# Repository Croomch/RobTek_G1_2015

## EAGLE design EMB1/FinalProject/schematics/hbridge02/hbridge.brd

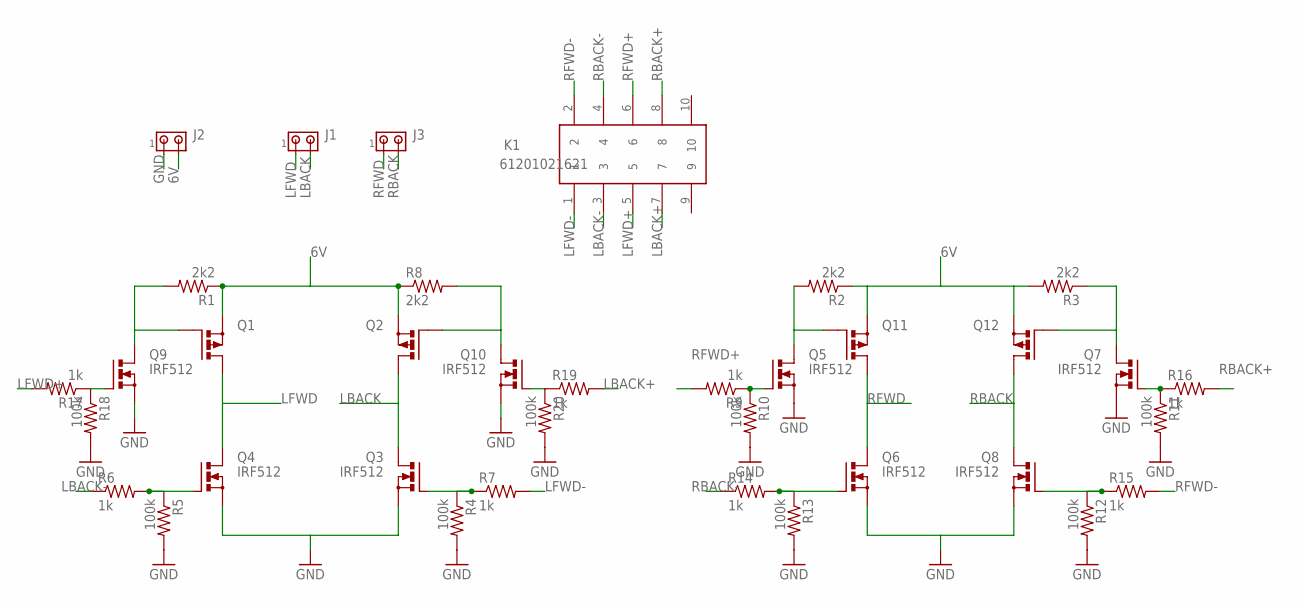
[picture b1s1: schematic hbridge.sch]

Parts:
J1, J2, J3: MTA02-100; 10X02MTA
K1: 61201021621
Q1, Q2, Q11, Q12: PMOSFET_PTO220BV; TO220BV
Q3, Q4, Q5, Q6, Q7, Q8, Q9, Q10: IRF512; TO220BV
R1, R2, R3, R8: 2k2; 0204/7
R4, R5, R10, R11, R12, R13, R18, R20: 100k; 0204/7
R6, R7, R9, R14, R15, R16, R17, R19: 1k; 0204/7

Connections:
6V: J2.2, Q1.S, Q2.S, Q11.S, Q12.S, R1.1, R2.1, R3.2, R8.1
GND: J2.1, Q3.S, Q4.S, Q5.S, Q6.S, Q7.S, Q8.S, Q9.S, Q10.S, R4.2, R5.2, R10.2, R11.2, R12.2, R13.2, R18.2, R20.2
LBACK: J1.2, Q2.D, Q3.D
LBACK+: K1.7, R19.2
LBACK-: K1.3, R6.1
LFWD: J1.1, Q1.D, Q4.D
LFWD+: K1.5, R17.2
LFWD-: K1.1, R7.2
unnamed: Q3.G, R4.1, R7.1
unnamed: Q2.G, Q10.D, R8.2
unnamed: Q4.G, R5.1, R6.2
unnamed: Q1.G, Q9.D, R1.2
unnamed: Q8.G, R12.1, R15.1
unnamed: Q7.G, R11.1, R16.1
unnamed: Q6.G, R13.1, R14.2
unnamed: Q5.G, R9.1, R10.1
unnamed: Q5.D, Q11.G, R2.2
unnamed: Q10.G, R19.1, R20.1
unnamed: Q9.G, R17.1, R18.1
unnamed: Q7.D, Q12.G, R3.1
RBACK: J3.2, Q8.D, Q12.D
RBACK+: K1.8, R16.2
RBACK-: K1.4, R14.1
RFWD: J3.1, Q6.D, Q11.D
RFWD+: K1.6, R9.2
RFWD-: K1.2, R15.2

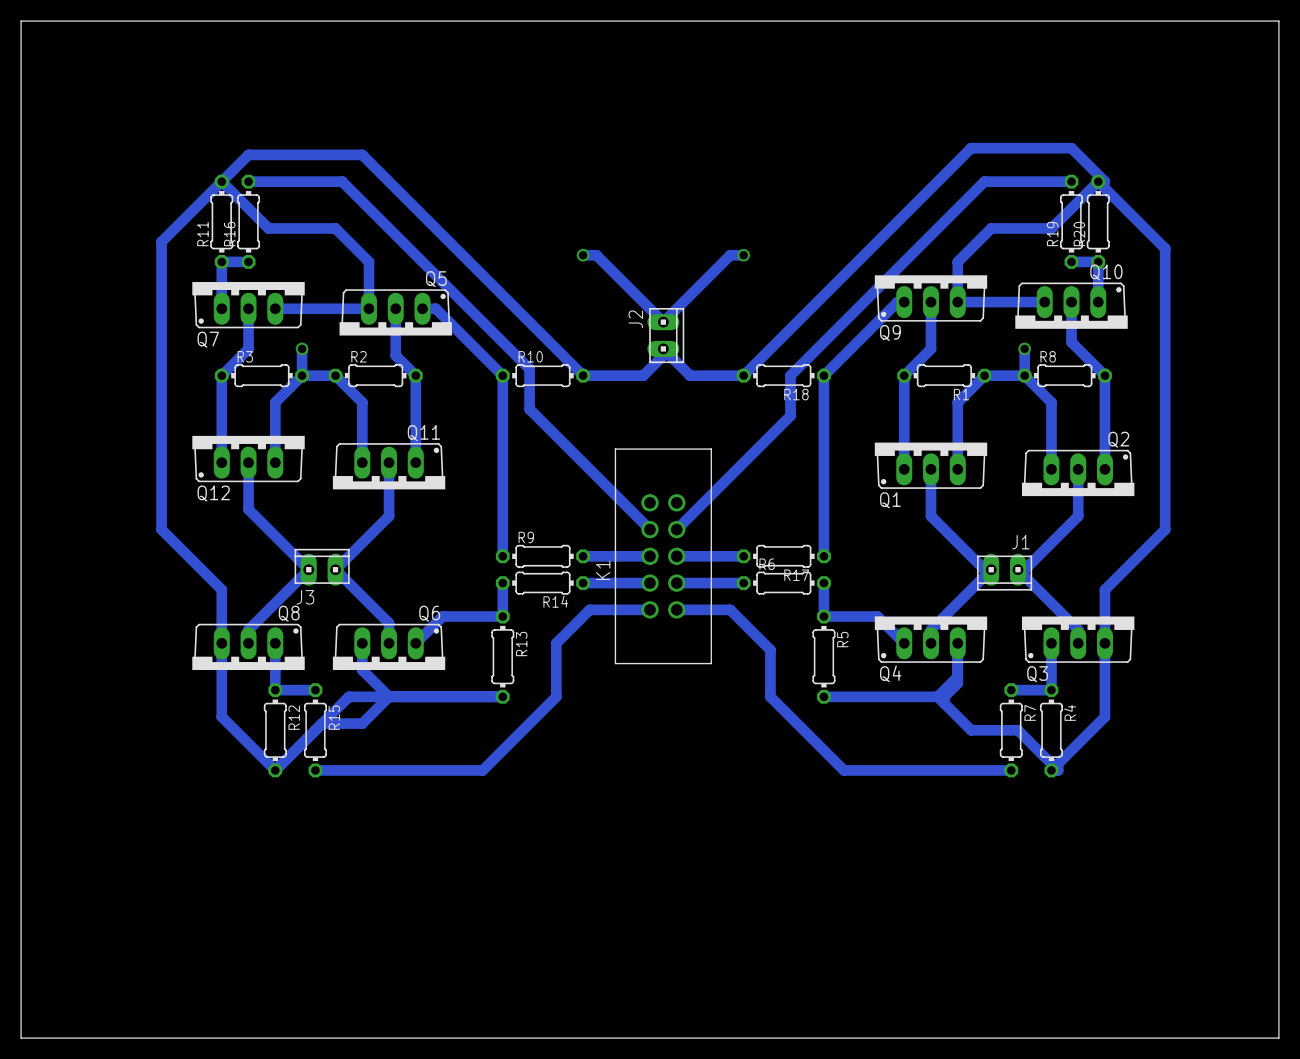
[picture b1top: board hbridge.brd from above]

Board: 2 copper layers, 119.4 x 96.5 mm, 36 parts (0 on the bottom side), 26 nets.

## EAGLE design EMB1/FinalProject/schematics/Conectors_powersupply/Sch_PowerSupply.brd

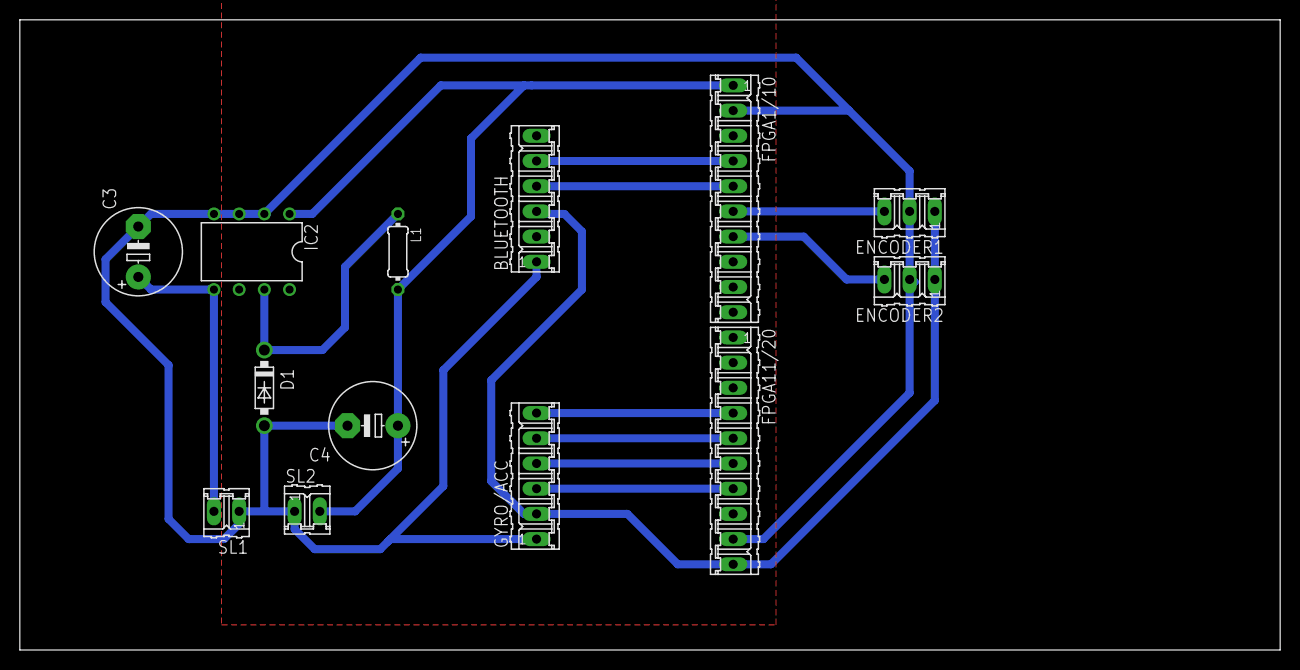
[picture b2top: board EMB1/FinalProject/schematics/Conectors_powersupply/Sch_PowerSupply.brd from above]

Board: 2 copper layers, 127.0 x 63.5 mm, 13 parts (0 on the bottom side), 13 nets.

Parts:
BLUETOOTH: 06P
C3: 22; E5-8,5
C4: 220; E5-8,5
D1: 1N5817-B; DO41-7.6
ENCODER1, ENCODER2: 03P
FPGA1/10, FPGA11/20: 10P
GYRO/ACC: 06P
IC2: LM2574N-3.3; DIL08
L1: 0204/7
SL1, SL2: 02P

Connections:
3.3V: BLUETOOTH.3, ENCODER1.1, ENCODER2.1, FPGA11/20.10, GYRO/ACC.2
5V: C4.+, FPGA1/10.1, IC2.1, L1.2, SL2.2
15V: C3.+, IC2.5, SL1.2
CL: FPGA11/20.4, GYRO/ACC.6
GND: BLUETOOTH.1, C3.-, C4.-, D1.A, ENCODER1.2, ENCODER2.2, FPGA1/10.2, FPGA11/20.9, GYRO/ACC.1, IC2.2, IC2.3, IC2.4, SL1.1, SL2.1
MISO: FPGA11/20.5, GYRO/ACC.5
MOSI: FPGA11/20.7, GYRO/ACC.3
unnamed: D1.C, IC2.7, L1.1
RX-I: BLUETOOTH.5, FPGA1/10.4
SCL: FPGA11/20.6, GYRO/ACC.4
SIGNAL1: ENCODER1.3, FPGA1/10.6
SIGNAL2: ENCODER2.3, FPGA1/10.7
TX-O: BLUETOOTH.4, FPGA1/10.5

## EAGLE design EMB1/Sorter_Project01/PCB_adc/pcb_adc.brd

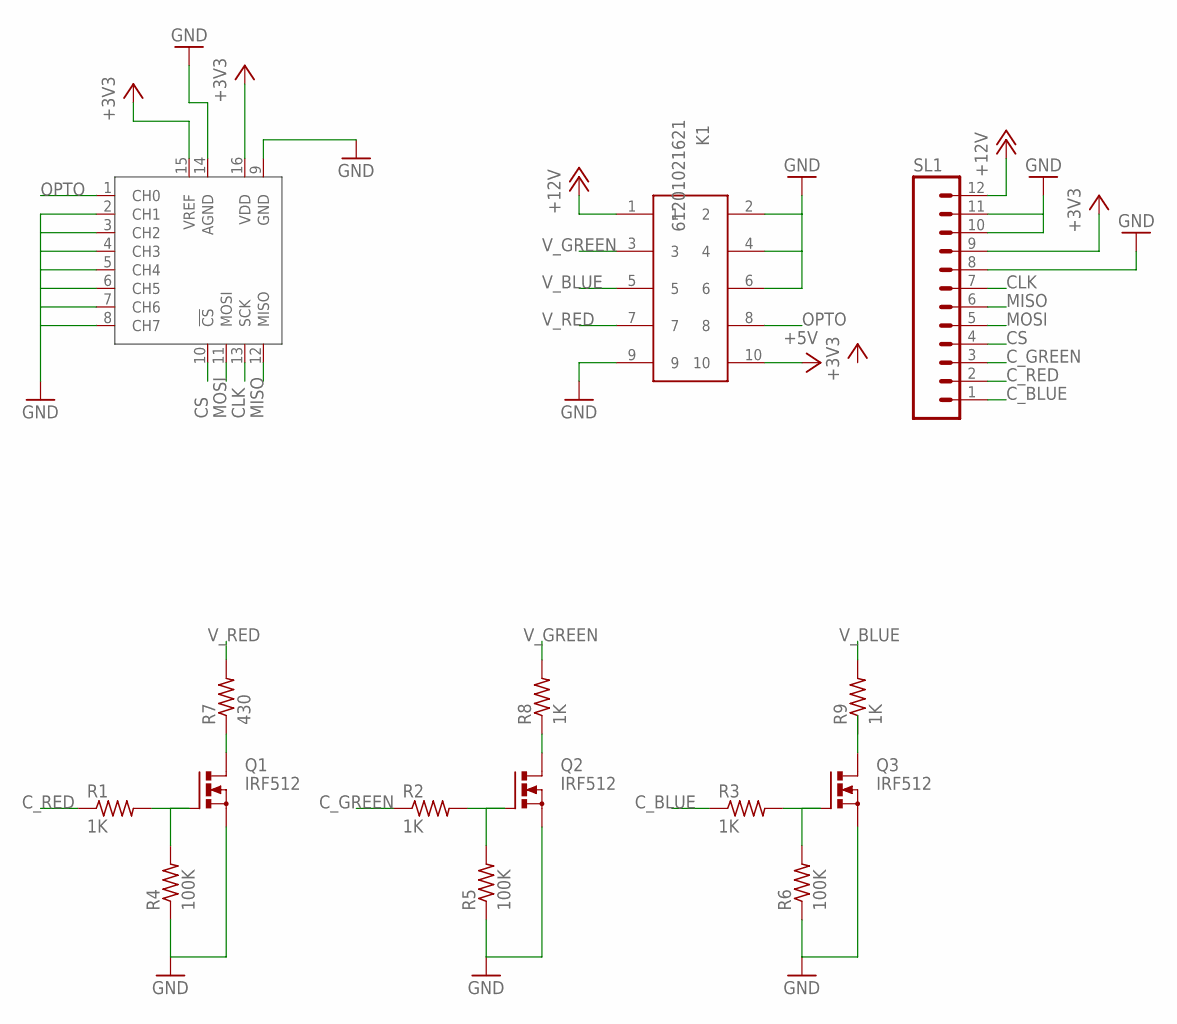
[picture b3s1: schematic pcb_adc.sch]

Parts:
K1: 61201021621
Q1, Q2, Q3: IRF512; TO220BV
R1, R2, R3, R8, R9: 1K; 0204/7
R4, R5, R6: 100K; 0204/7
R7: 430; 0204/7
SL1: M12; 12P
U$1: MCP3008P; DIL16

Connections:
+3V3: SL1.9, U$1.15 (VREF), U$1.16 (VDD)
+5V: K1.10
+12V: K1.1, SL1.12
CLK: SL1.7, U$1.13 (SCK)
CS: SL1.4, U$1.10 (!CS)
C_BLUE: R3.1, SL1.1
C_GREEN: R2.1, SL1.3
C_RED: R1.1, SL1.2
GND: K1.2, K1.4, K1.6, K1.9, Q1.S, Q2.S, Q3.S, R4.1, R5.1, R6.1, SL1.8, SL1.10, SL1.11, U$1.2 (CH1), U$1.3 (CH2), U$1.4 (CH3), U$1.5 (CH4), U$1.6 (CH5), U$1.7 (CH6), U$1.8 (CH7), U$1.9 (GND), U$1.14 (AGND)
MISO: SL1.6, U$1.12 (MISO)
MOSI: SL1.5, U$1.11 (MOSI)
unnamed: Q1.G, R1.2, R4.2
unnamed: Q2.G, R2.2, R5.2
unnamed: Q3.G, R3.2, R6.2
unnamed: Q1.D, R7.1
unnamed: Q2.D, R8.1
unnamed: Q3.D, R9.1
OPTO: K1.8, U$1.1 (CH0)
V_BLUE: K1.5, R9.2
V_GREEN: K1.3, R8.2
V_RED: K1.7, R7.2

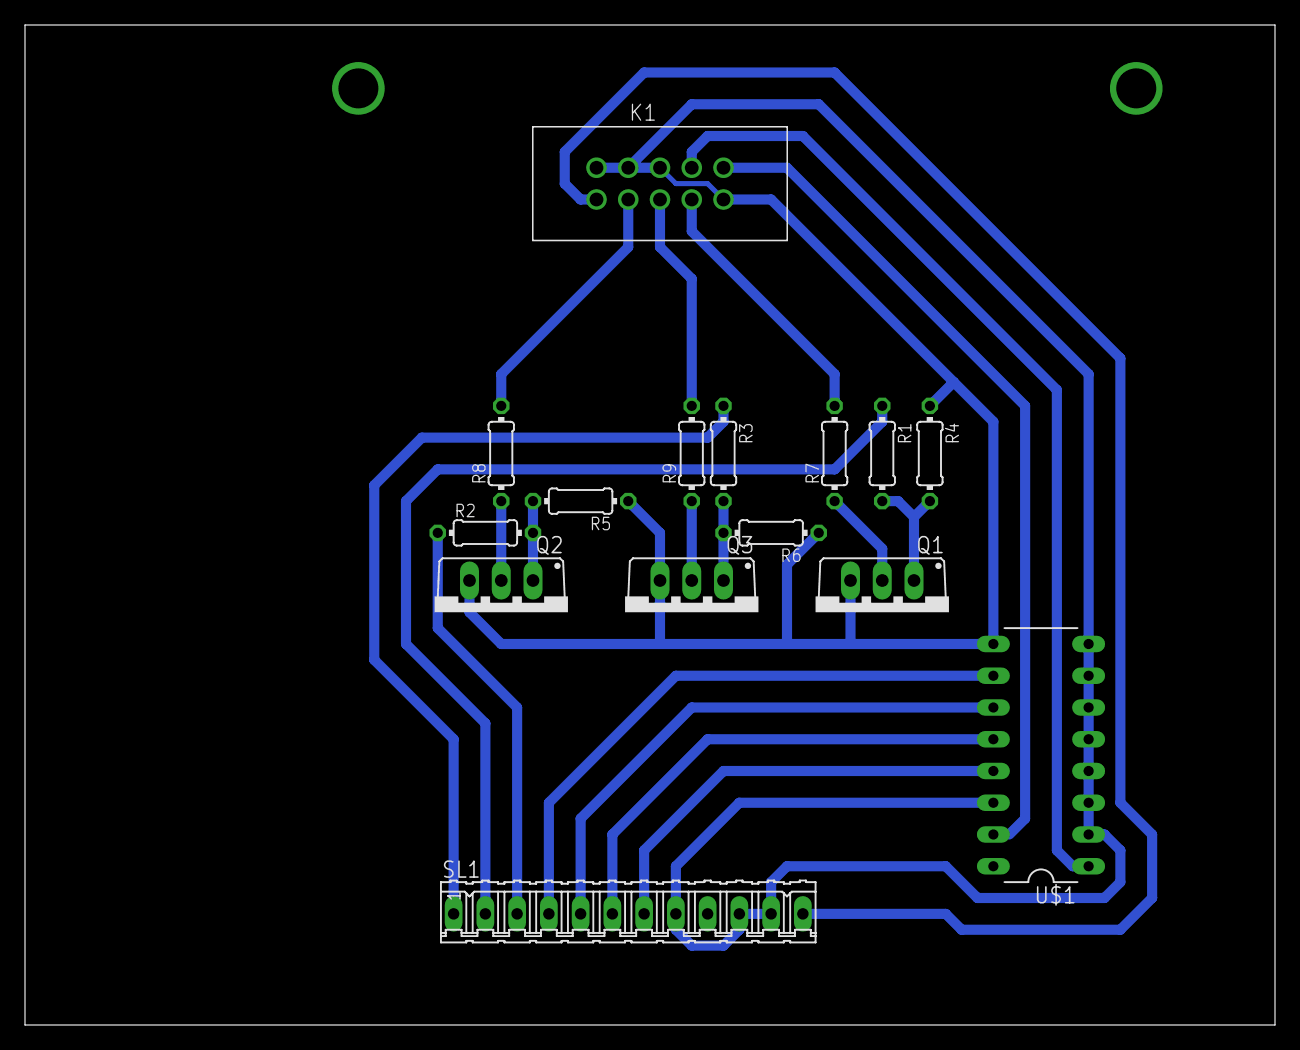
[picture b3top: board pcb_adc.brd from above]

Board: 2 copper layers, 100.0 x 80.0 mm, 15 parts (0 on the bottom side), 20 nets.

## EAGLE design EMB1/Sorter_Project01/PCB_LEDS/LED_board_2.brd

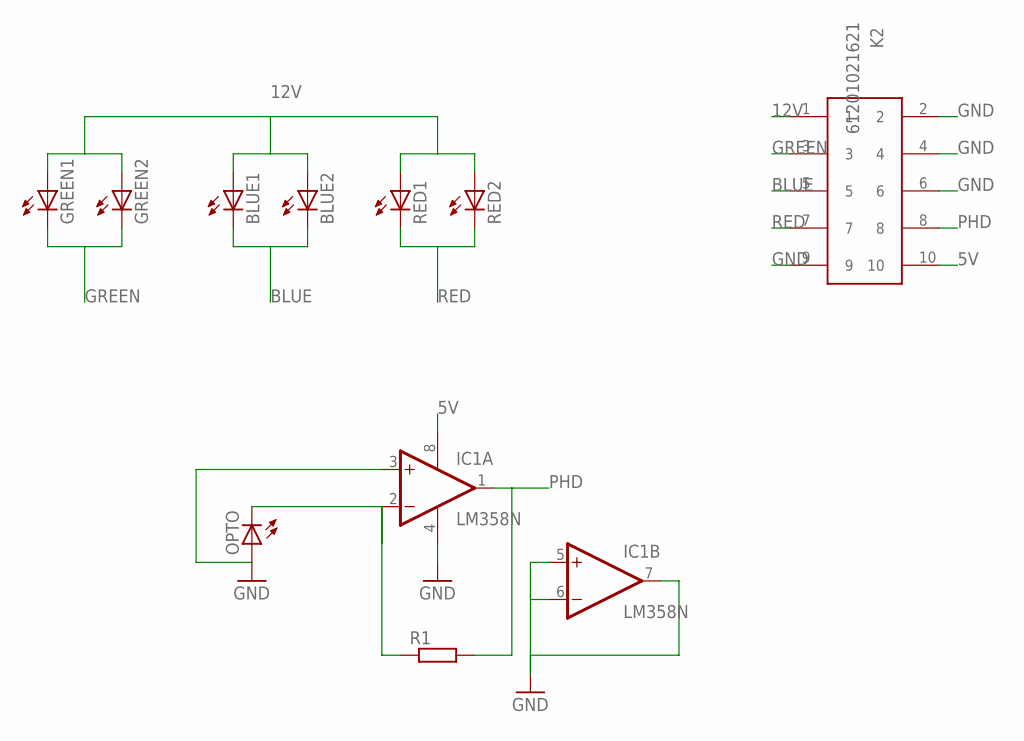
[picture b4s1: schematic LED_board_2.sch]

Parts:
BLUE1, BLUE2: LED5MM
GREEN1, GREEN2: LED5MM
IC1: LM358N; DIL08
K2: 61201021621
OPTO: LED5MM
R1: R-EU_0207/10; 0207/10
RED1, RED2: LED5MM

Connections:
5V: IC1.8 (V+), K2.10
12V: BLUE1.A, BLUE2.A, GREEN1.A, GREEN2.A, K2.1, RED1.A, RED2.A
BLUE: BLUE1.K (C), BLUE2.K (C), K2.5
GND: IC1.3 (+IN), IC1.4 (V-), IC1.5 (+IN), IC1.6 (-IN), IC1.7 (OUT), K2.2, K2.4, K2.6, K2.9, OPTO.A
GREEN: GREEN1.K (C), GREEN2.K (C), K2.3
unnamed: IC1.2 (-IN), OPTO.K (C), R1.1
PHD: IC1.1 (OUT), K2.8, R1.2
RED: K2.7, RED1.K (C), RED2.K (C)

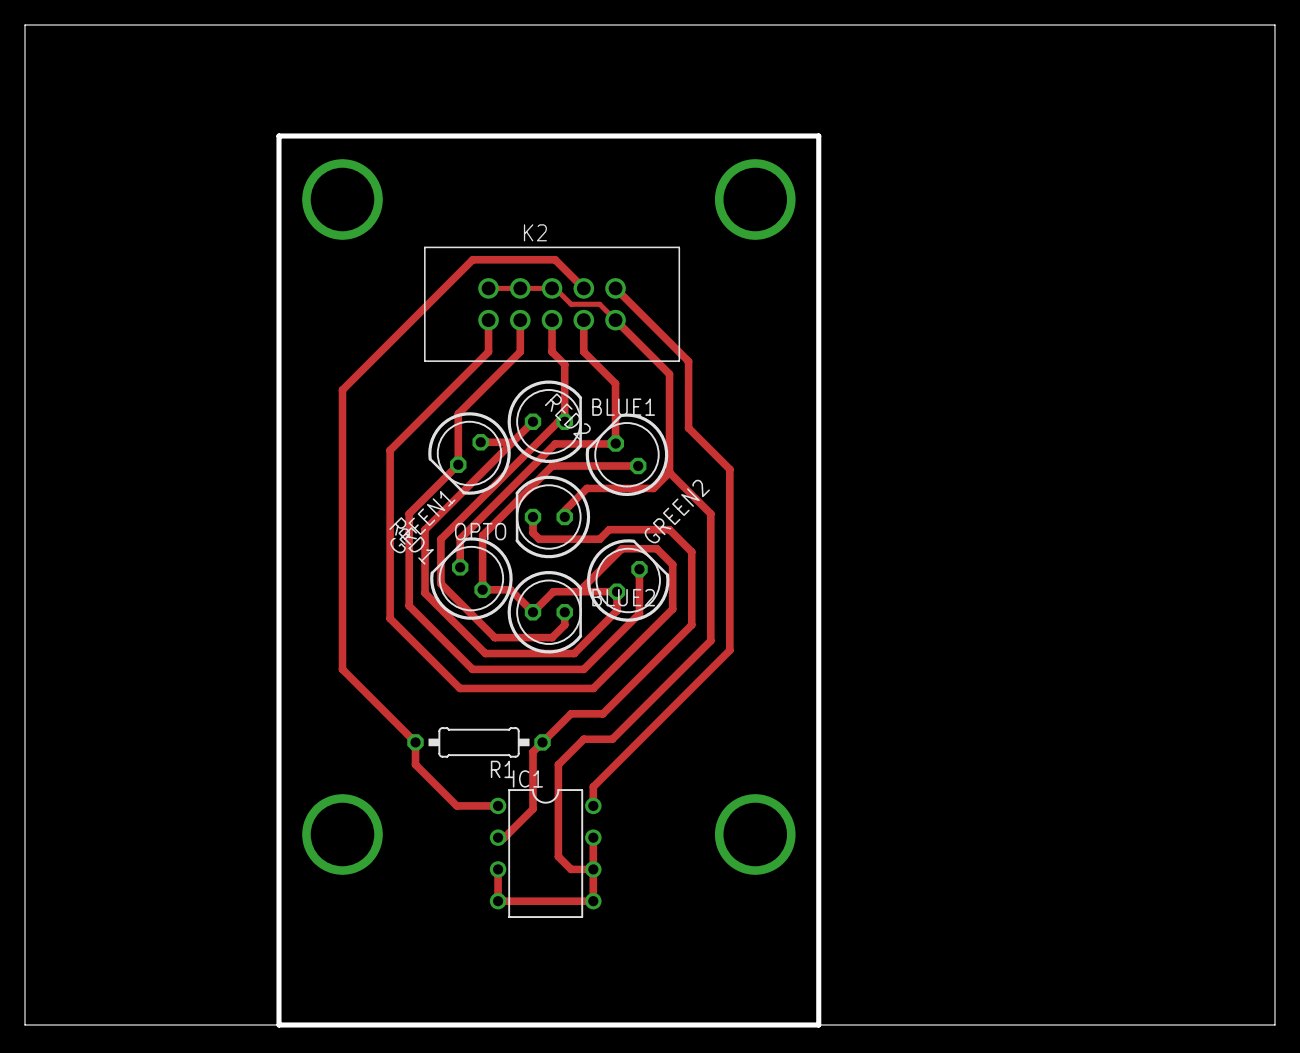
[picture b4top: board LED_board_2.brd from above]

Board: 2 copper layers, 100.0 x 80.0 mm, 10 parts (0 on the bottom side), 8 nets.

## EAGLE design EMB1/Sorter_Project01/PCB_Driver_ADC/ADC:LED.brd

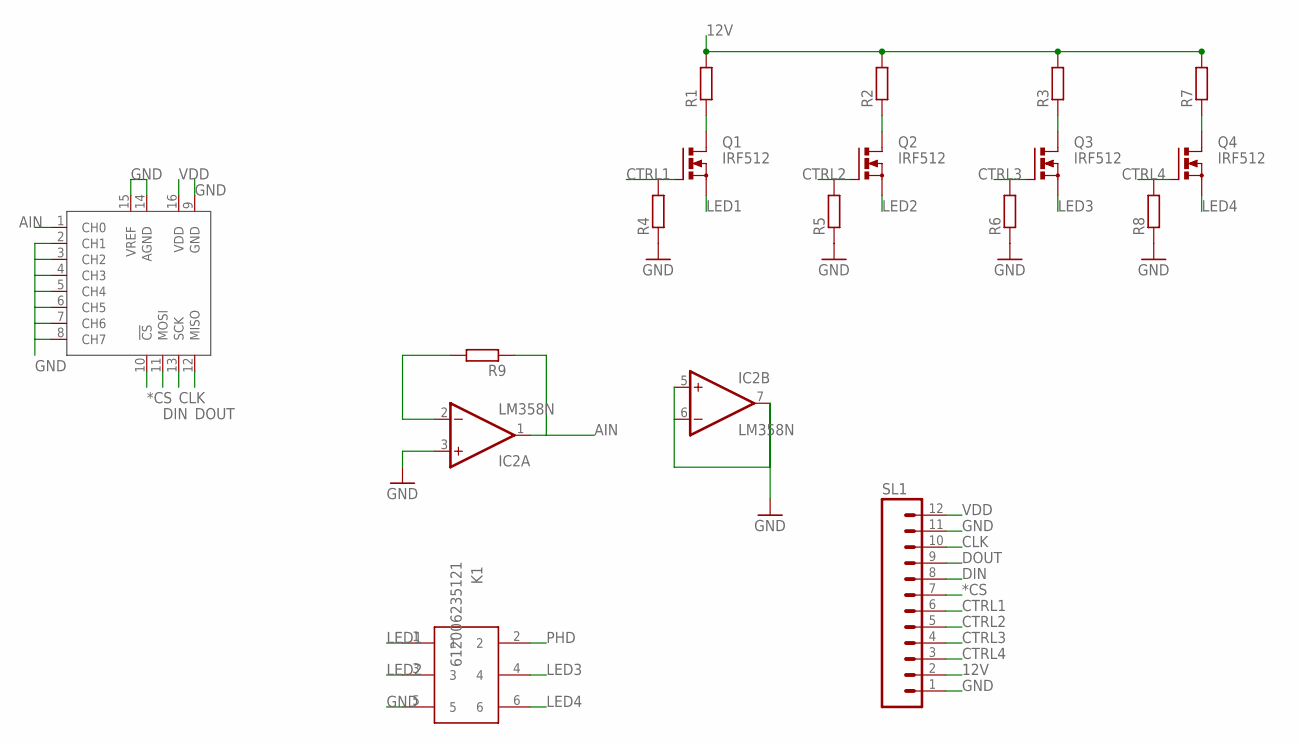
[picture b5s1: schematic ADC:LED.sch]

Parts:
IC2: LM358N; DIL08
K1: 612006235121
Q1, Q2, Q3, Q4: IRF512; TO220BV
R1, R2, R3, R4, R5, R6, R7, R8, R9: R-EU_0204/7; 0204/7
SL1: M12; 12P
U$2: MCP3008P; DIL16

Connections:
12V: R1.2, R2.2, R3.2, R7.2, SL1.2
*CS: SL1.7, U$2.10 (!CS)
AIN: IC2.1 (OUT), R9.1, U$2.1 (CH0)
CLK: SL1.10, U$2.13 (SCK)
CTRL1: Q1.G, R4.2, SL1.6
CTRL2: Q2.G, R5.2, SL1.5
CTRL3: Q3.G, R6.2, SL1.4
CTRL4: Q4.G, R8.2, SL1.3
DIN: SL1.8, U$2.11 (MOSI)
DOUT: SL1.9, U$2.12 (MISO)
GND: IC2.3 (+IN), IC2.4 (V-), IC2.5 (+IN), IC2.6 (-IN), IC2.7 (OUT), K1.5, R4.1, R5.1, R6.1, R8.1, SL1.1, SL1.11, U$2.2 (CH1), U$2.3 (CH2), U$2.4 (CH3), U$2.5 (CH4), U$2.6 (CH5), U$2.7 (CH6), U$2.8 (CH7), U$2.9 (GND), U$2.14 (AGND), U$2.15 (VREF)
LED1: K1.1, Q1.S
LED2: K1.3, Q2.S
LED3: K1.4, Q3.S
LED4: K1.6, Q4.S
unnamed: Q1.D, R1.1
unnamed: Q2.D, R2.1
unnamed: Q3.D, R3.1
unnamed: Q4.D, R7.1
PHD: IC2.2 (-IN), K1.2, R9.2
VDD: IC2.8 (V+), SL1.12, U$2.16 (VDD)

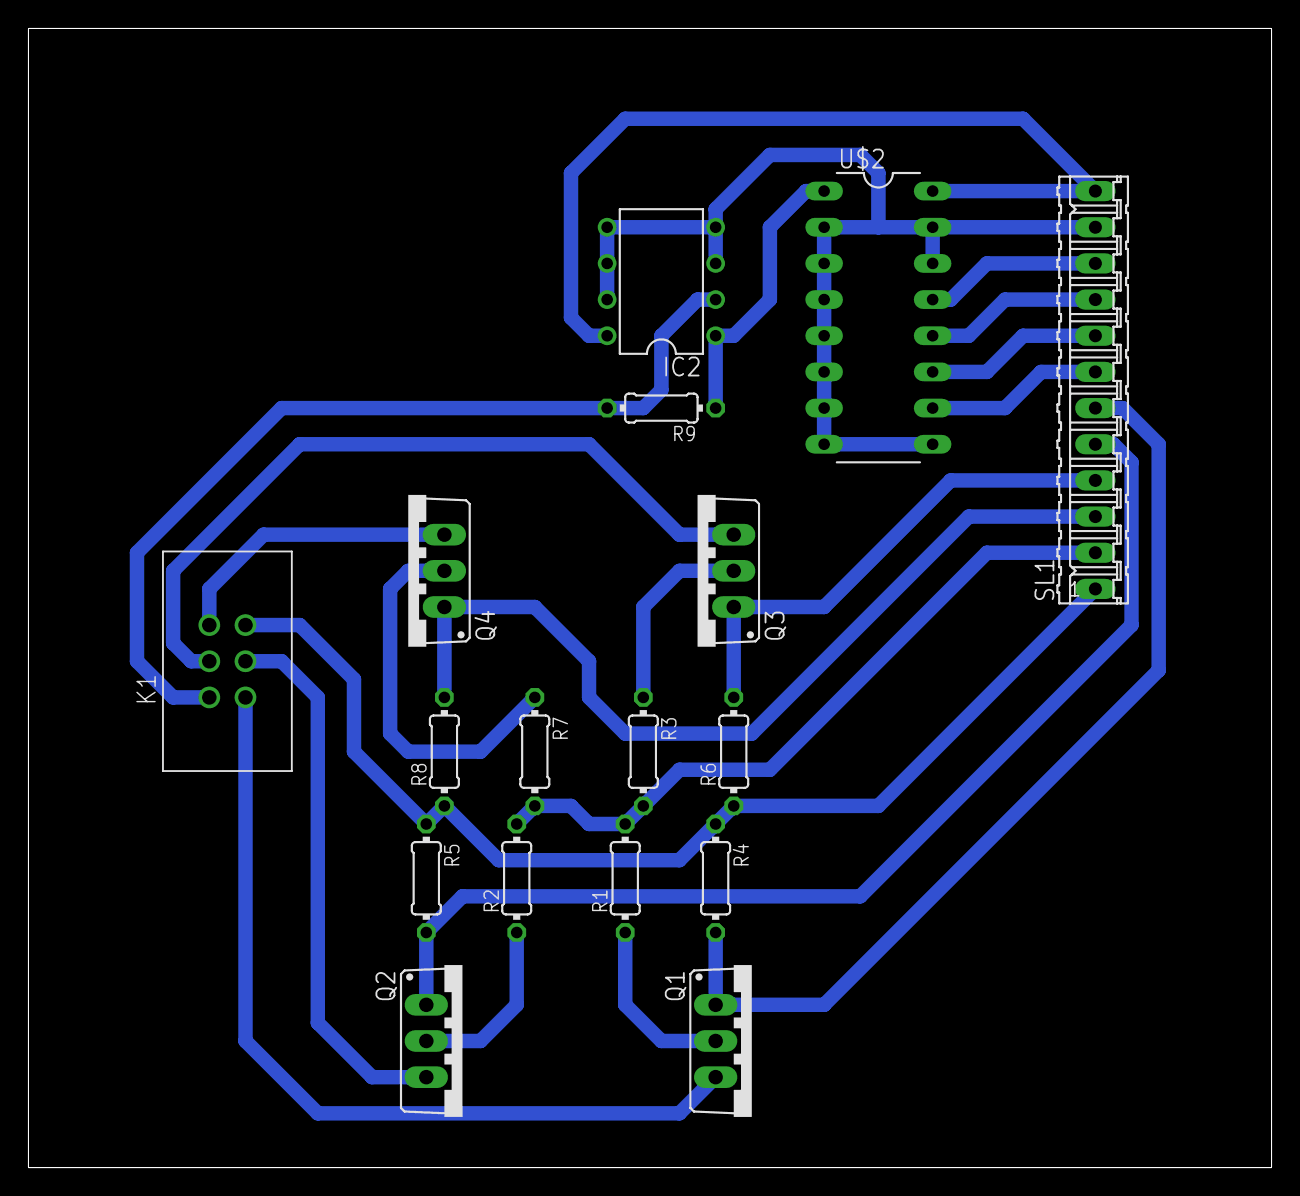
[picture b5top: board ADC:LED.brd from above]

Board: 2 copper layers, 87.3 x 80.0 mm, 17 parts (0 on the bottom side), 21 nets.

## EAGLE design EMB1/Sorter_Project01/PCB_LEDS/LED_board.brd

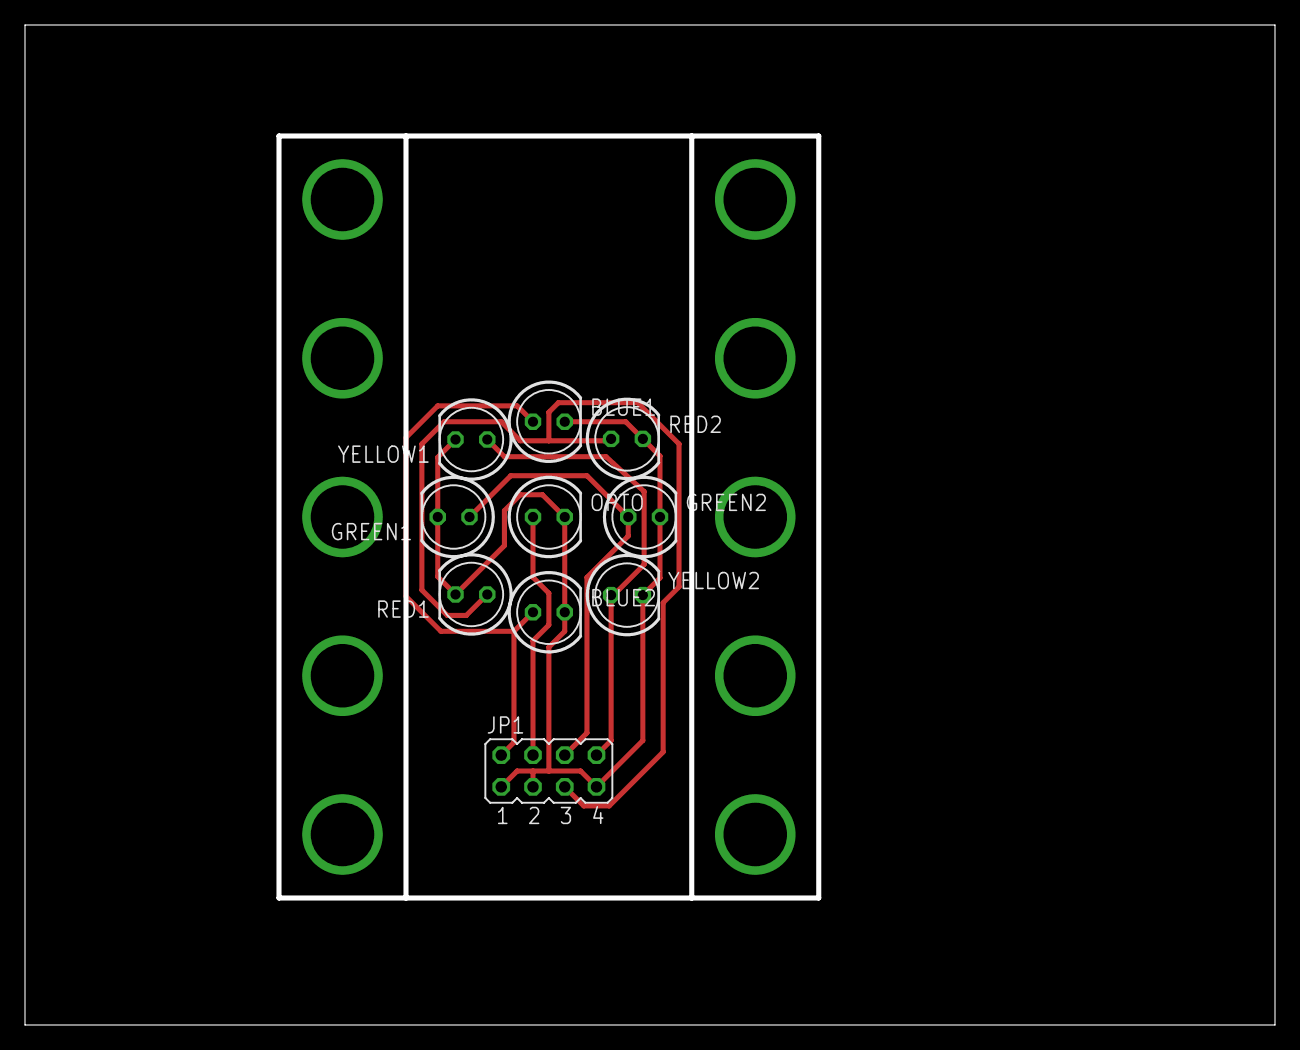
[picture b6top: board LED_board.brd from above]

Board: 2 copper layers, 100.0 x 80.0 mm, 10 parts (0 on the bottom side), 6 nets.

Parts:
BLUE1, BLUE2: LED5MM
GREEN1, GREEN2: LED5MM
JP1: JP4Q
OPTO: LED5MM
RED1, RED2: LED5MM
YELLOW1, YELLOW2: LED5MM

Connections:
GND: BLUE1.K, BLUE2.K, GREEN1.K, GREEN2.K, JP1.1, JP1.3, JP1.7, OPTO.K, RED1.K, RED2.K, YELLOW1.K, YELLOW2.K
unnamed: JP1.5, RED1.A, RED2.A
unnamed: GREEN1.A, GREEN2.A, JP1.6
unnamed: BLUE1.A, BLUE2.A, JP1.2
unnamed: JP1.8, YELLOW1.A, YELLOW2.A
unnamed: JP1.4, OPTO.A

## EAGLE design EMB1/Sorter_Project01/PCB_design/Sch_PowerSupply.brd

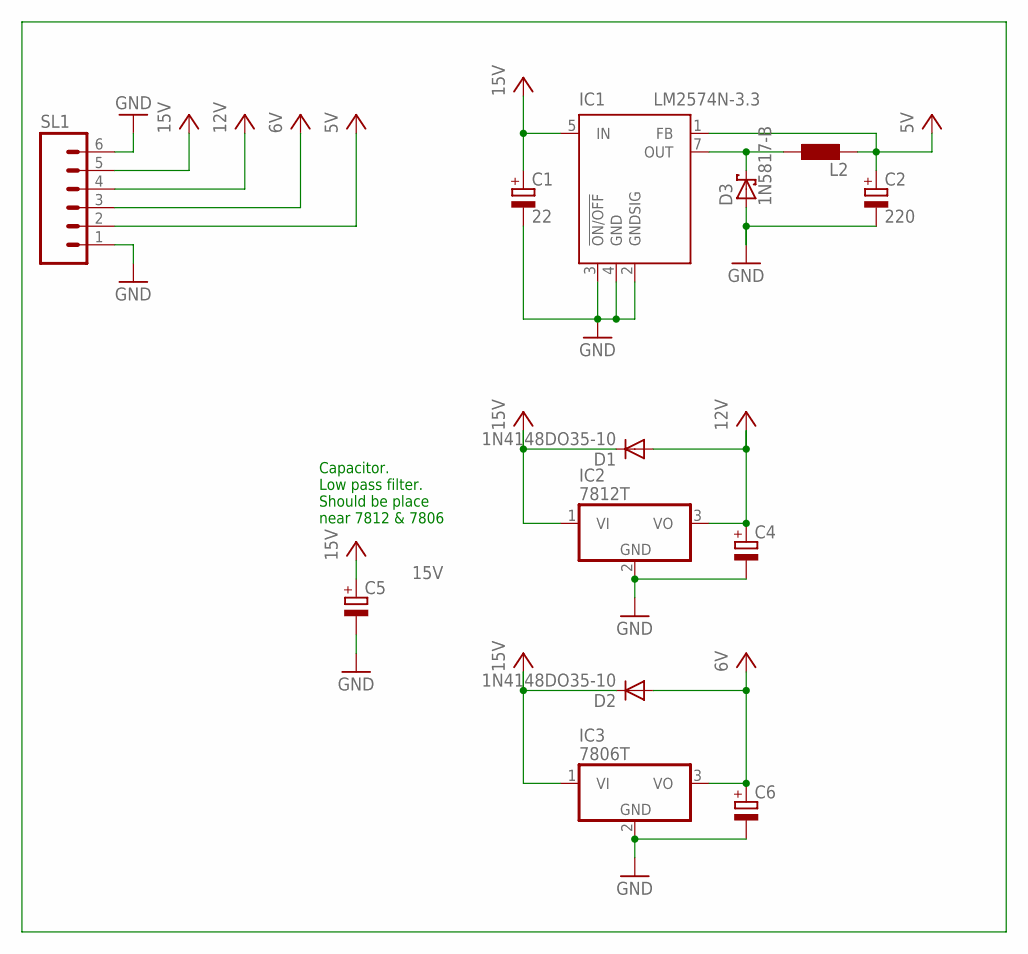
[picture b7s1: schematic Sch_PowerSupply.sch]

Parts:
C1: 22; E5-8,5
C2: 220; E5-8,5
C4, C5, C6: CPOL-EUE5-8.5; E5-8,5
D1, D2: 1N4148DO35-10; DO35-10
D3: 1N5817-B; DO41-7.6
IC1: LM2574N-3.3; DIL08
IC2: 7812T; TO220H
IC3: 7806T; TO220H
L2: L0204/7; 0204/7
SL1: M06; 06P

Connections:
5V: C2.+, IC1.1 (FB), L2.2, SL1.2
6V: C6.+, D2.A, IC3.3 (VO), SL1.3
12V: C4.+, D1.A, IC2.3 (VO), SL1.4
15V: C1.+, C5.+, D1.C, D2.C, IC1.5 (IN), IC2.1 (VI), IC3.1 (VI), SL1.5
GND: C1.-, C2.-, C4.-, C5.-, C6.-, D3.A, IC1.2 (GNDSIG), IC1.3 (!ON/OFF), IC1.4 (GND), IC2.2 (GND), IC3.2 (GND), SL1.1, SL1.6
unnamed: D3.C, IC1.7 (OUT), L2.1

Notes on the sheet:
Capacitor. Low pass filter. Should be place near 7812 & 7806

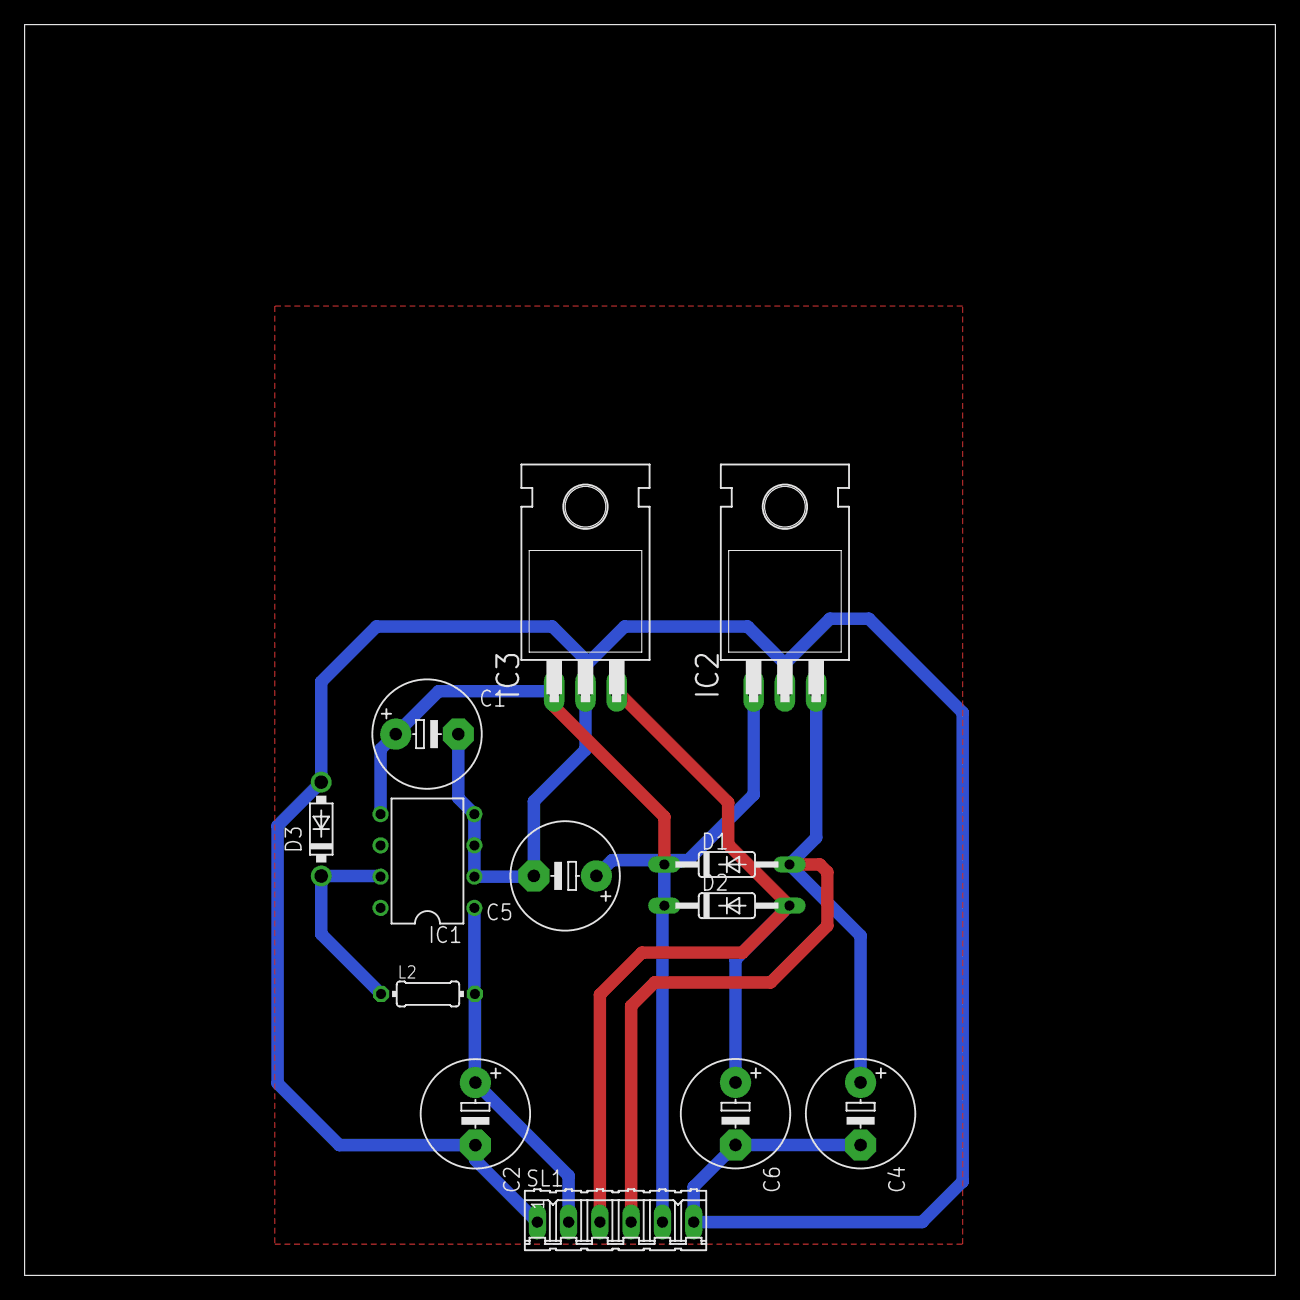
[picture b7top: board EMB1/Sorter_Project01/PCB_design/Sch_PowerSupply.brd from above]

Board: 2 copper layers, 101.6 x 101.6 mm, 13 parts (0 on the bottom side), 6 nets.

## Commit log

2015-09-17 gitignore added
2015-09-18 git ignore
2015-09-18 more ignore
2015-09-18 readme
2015-09-18 embi
2015-09-18 EMB project (FSM)
2015-09-19 Files for AI/LEGO
2015-09-19 Lego - Test programs for the robot (sensor test and follow line)
2015-09-22 FSM test bench and update on BTN test bench
2015-09-24 file update and diagrams added
2015-09-24 AI line follow - improved version
2015-09-29 Code for the new robot designe
2015-10-05 skeletons and todo
2015-10-05 added EMB1/Sorter_Project01/PCB_design/Sch_PowerSupply.brd
2015-10-08 gitignore updated
2015-10-08 New board
2015-10-08 board and ignore update
2015-10-08 brd update
2015-10-09 LED board to put on the slider (excluding LED drivers)
2015-10-11 Unfinished code for the sokoban solver and test maps
2015-10-11 report updated
2015-10-13 code update, still work in progress
2015-10-14 added images and actualized report
2015-10-15 actualized repot
2015-10-16 report updated, restructured the last part
2015-10-16 put figures in subfolder
2015-10-19 Act Report
2015-10-19 report update
2015-10-19 report titlepage added
2015-10-19 report: last subsection added
2015-10-19 Turn right program
2015-10-21 Sokoban solver, able to find the shortest solution, but does not store the path yet
2015-10-21 gitignore updated to exclude temp/backup files (*~)
2015-10-21 Heuristic add to the sokoban solver
2015-10-23 data added for powersupply and sokoban maps
2015-10-25 new board design for leds with 2x3 connector
2015-10-25 PCB design for LED driver and ADC board
2015-10-25 Driver/ADC board modified
2015-10-26 Printed schematic ADC/LEDS
2015-10-26 Report for brick sorter added
2015-10-27 renaming files... windows does NOT allow : in file names :(
2015-10-27 report structure updated
2015-10-27 moved old board designs
2015-10-27 New LED Board design
2015-10-27 new boards
2015-10-27 updated PCB design
2015-10-28 VHDL code files
2015-10-28 report images added
2015-10-28 VHDL updated, now the blinking works due to bug pulsing data-updated for too long
2015-10-28 VHDL code with usb comunication
2015-10-28 something changed!
2015-10-28 new project added
2015-10-28 useless changes
2015-10-29 VHDL files adjusted to accomondate changing and readign different parameters through uTosNet
2015-10-29 PC_interface program added
2015-10-29 Updated PC_interface
2015-10-29 pc to fpga program
2015-10-29 Added new program. Writing working, working on reading
2015-10-29 Added code to read constantly the FPGA and print it on screen
2015-10-30 report updated with powersupply text and matlab script added
2015-10-30 matlab script changed to make graph, not complete yet
2015-10-30 Changes in the pc interface and lower Switch frequency for LEDs
2015-10-30 LED_driver report modified
2015-10-30 amplifier data, update fpga code
2015-10-31 Report section and image added
2015-10-31 report and SPI update
2015-10-31 report and motor control update
2015-10-31 Changes in FPGA PC registers
2015-10-31 SPI to ADC fixed
2015-10-31 typo fix in FSM
2015-10-31 Changes in sorter treshold selection
2015-10-31 motor control update
2015-10-31 fixed brick counter
2015-10-31 New cpp project for PC interface
2015-10-31 space optimization only 99% of all slices used :)
2015-10-31 asdf
2015-10-31 bug fixed: timeout
2015-11-01 report updated, frontpage and design completed, data from experiments added.
2015-11-01 subsection conclusions added to report
2015-11-01 updated report section about system tests
2015-11-01 small changes to the report
2015-11-01 New appendix
2015-11-01 updated report with a couple of adjustments
2015-11-01 Hand in folder
2015-11-01 merged stuff
2015-11-01 report updated with small changes
2015-11-01 cmakefile added
2015-11-01 supervisor added
2015-11-02 sokoban solver now with path remembered, gitignore updated and report structure for AI updated
2015-11-02 Functions to turn left and back added
2015-11-05 final project folder
2015-11-05 old images removed
2015-11-05 Project Description
2015-11-12 code project added
2015-11-12 vhdl ppr
2015-11-12 Added communication behaviour
2015-11-12 code for motorcontrol added
2015-11-12 SPI interface updated to match gyro/accenerometer
2015-11-13 top module updated
2015-11-13 report updated: software-graph and -heuristic
2015-11-14 software part of the report updated
2015-11-14 report: physical system updated
2015-11-16 actualized Communication.vhd
2015-11-16 COnverted the sokoban path to something understandble by the robot (L,R,F,B)
2015-11-16 Changes on communication.vhd. Im going to test and build the code in another project. If the file is problematic you can delete it.
2015-11-16 sokoban maps added
2015-11-17 Actualized TurnRigt Program. It includes all the funtions for turning in all directions. Added to a while loop a for loop to complete certain circuit. Added some kind of integral action to the follow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
2015-11-18 code tested further and maps added
2015-11-19 ignore updated
2015-11-19 utosnet
2015-11-19 angle thingy
2015-11-19 ppr file + gitignore
2015-11-19 other files
2015-11-19 angle predictor updated
2015-11-19 something random
2015-11-19 muhahaha crashing everything
2015-11-19 Fixed warning
2015-11-20 Added FPGA/bluetooth/sensor connection PCB
2015-11-20 changes in pcb
2015-11-22 project files
2015-11-22 Changed the way the robot uses the given path
2015-11-23 improved sokoban solver
2015-11-23 path correctly converted
2015-11-23 added map
2015-11-23 improved speed of the solver
2015-11-26 sokoban change
2015-12-01 Script race lego
2015-12-01 project files and report
2015-12-02 New PID module vhdl.
2015-12-03 Changes in vhdl model
2015-12-03 now requesting data from the accelerometer
2015-12-03 Changes in pid_controller
2015-12-03 filesystem changed
2015-12-03 fixed tx defines to read from imu
2015-12-03 changes in topmodule and motorcontrol. Set the motor output configuration
2015-12-03 Spi clk slowed down
2015-12-03 Changes and trials
2015-12-04 brd put in folders
2015-12-04 SPI module updated to send data too
2015-12-04 constraint file changed - comments added only
2015-12-04 scramble code
2015-12-07 Changes in AI report
2015-12-07 Changes on topmodule, SPI to 16
2015-12-07 Softwaresection of AI report updated
2015-12-07 changes in report
2015-12-08 software test put back into the software section
2015-12-10 Changes in PID controller
2015-12-10 SPI module hopefully fixed
2015-12-10 changes again
2015-12-10 PID controller fixed (?)
2015-12-10 new statemachine design added
2015-12-10 fixed spi module
2015-12-10 topmodule updated: motor state machine started
2015-12-11 AI report actualization
2015-12-11 Introduction and changes in hardwaretest
2015-12-11 Changes in hardware conclusion
2015-12-11 Added Conclusion
2015-12-11 small adjustments to the report
2015-12-11 Added acceleration filter
2015-12-11 Report updated and conclusion to HW chapter added
2015-12-14 Fixed SPI module, added read full x register, changed mean filter to convert the data from the accelerometer
2015-12-15 Changed port configurations for pwms and fixed MeanFilter data conversion
2015-12-16 Changes in top module, counter to wait between direction changes in the motor
2015-12-17 topmodule updated: motor control timeout expanded (untested)
2015-12-18 code updated: made 16 bit and PID fixed to give good results
2015-12-19 code updated, utos removed
2015-12-19 Report documents for structure added
2015-12-19 Software intro of the report written
2015-12-20 small changes before revert
2015-12-20 working now for low p values with 8 bit..
2015-12-20 Code updated
2015-12-20 conclusion to the report added and some small code changes
2015-12-21 system test added
2015-12-21 Report updated: full system part added
2015-12-21 Changes in h-bridge description
2015-12-21 Changes infpga design figure
2015-12-21 Small smpeeling mistakes in Hbridge. Figures needed.
2015-12-21 fullsystem of segway described and section file for powersupply added.
2015-12-21 segway control part in software written.
2015-12-21 Conclusion to the physical part added
2015-12-21 spi and motorcontrol section added
2015-12-22 Schematics added to hbridge
2015-12-22 Powersupply section added
2015-12-22 discussion added
2015-12-22 small addition to motor control and conclusion of the sof part written
2015-12-22 Slight modifications to the PID and filter module
2015-12-22 Small changes added trhoughout the report
2015-12-22 proof reading the control probel section
2015-12-22 removing line breack
2015-12-22 removed us

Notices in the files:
parts and their libraries:
Wurth_Elektronik_Electromechanic_Wire_to: Copyright: Würth Elektronik
